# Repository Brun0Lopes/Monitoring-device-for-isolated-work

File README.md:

# Monitoring-device-for-isolated-work

This project is sponsored by JLCPCB, and will be used by workers when
they are carrying out activities in hazardous environments, to prevent
any serious accident from occurring.

Please visit https://jlcpcb.com/RAT

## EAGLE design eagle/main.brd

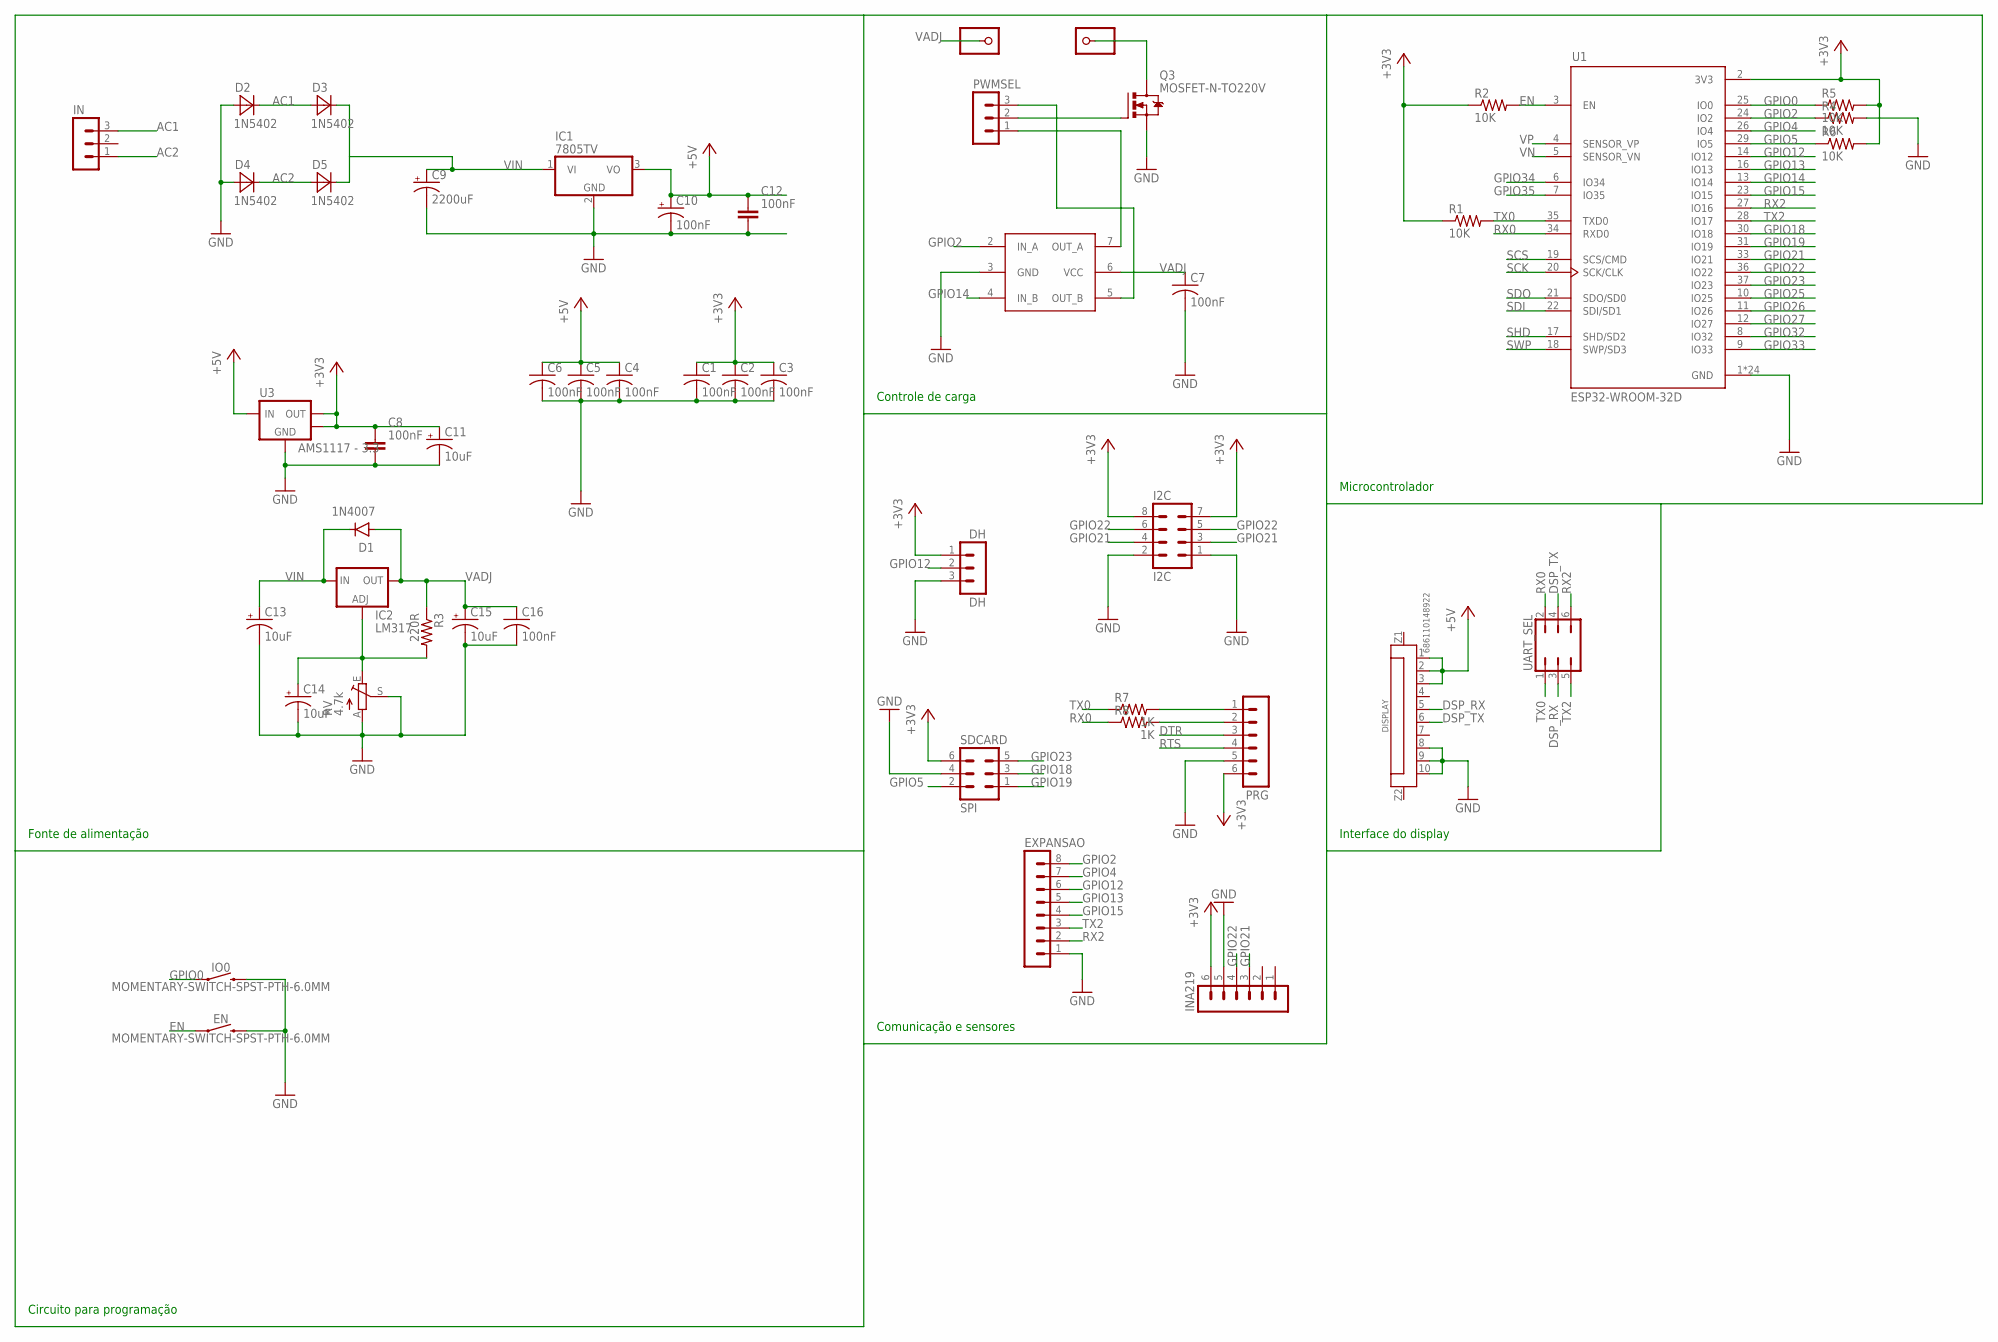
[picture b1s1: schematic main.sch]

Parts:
C1, C2, C3, C4, C5, C6, C7, C16: 100nF; C0805K
C8, C12: 100nF; CAPC2012X110
C9: 2200uF; E5-6
C10: 100nF; E2,5-5
C11, C15: 10uF; E2,5-5
C13, C14: 10uF; E2-4
D1: 1N4007; DO-41
D2, D3, D4, D5: 1N5402; DO201
DH: DH; MA03-1
DISPLAY: 686110148922
EN: MOMENTARY-SWITCH-SPST-PTH-6.0MM; TACTILE_SWITCH_PTH_6.0MM
EXPANSAO: MA08-1
I2C: I2C; MA04-2
IC1: 7805TV; TO220V
IC2: LM317; 317TS
IN: MA03-1
INA219: MA06-1
IO0: MOMENTARY-SWITCH-SPST-PTH-6.0MM; TACTILE_SWITCH_PTH_6.0MM
JP1: PINHD-1X01_2.54-S; 1X01-S
LOAD: PINHD-1X01_2.54-S; 1X01-S
PRG: MA06-1
PWMSEL: MA03-1
Q3: MOSFET-N-TO220V; TO220BV
R1, R2, R4, R5, R6: 10K; M0805
R3: 220R; 0207/5V
R7, R8: 1K; M0805
RV: 4.7k; RJ9W
SDCARD: SPI; MA03-2
U1: ESP32-WROOM-32D; MODULE_ESP32-WROOM-32D
U2: MC34151; DIL8
U3: AMS1117 - 3.3; SOT-223-3
UART_SEL: JP3Q

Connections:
+3V3: C1.1, C2.1, C3.1, C8.1, C11.+, DH.1, I2C.7, I2C.8, INA219.6, PRG.6, R1.1, R2.1, R5.2, R6.2, SDCARD.6, U1.2 (3V3), U3.2 (VOUT), U3.4 (HEATSINK)
+5V: C4.1, C5.1, C6.1, C10.+, C12.1, DISPLAY.1, DISPLAY.2, DISPLAY.3, IC1.3 (VO), U3.3 (VIN)
AC1: D2.C, D3.A, IN.3
AC2: D4.C, D5.A, IN.1
DSP_RX: DISPLAY.5, UART_SEL.3
DSP_TX: DISPLAY.6, UART_SEL.4
DTR: PRG.3
EN: EN.1, R2.2, U1.3 (EN)
GND: C1.2, C2.2, C3.2, C4.2, C5.2, C6.2, C7.2, C8.2, C9.-, C10.-, C11.-, C12.2, C13.-, C14.-, C15.-, C16.2, D2.A, D4.A, DH.3, DISPLAY.8, DISPLAY.9, DISPLAY.10, EN.3 (2), EXPANSAO.1, I2C.1, I2C.2, IC1.2 (GND), INA219.5, IO0.3 (2), PRG.5, Q3.S, R4.2, RV.A, RV.S, SDCARD.4, U1.1 (GND), U1.15 (GND), U1.38 (GND), U1.39_1 (GND), U1.39_2 (GND), U1.39_3 (GND), U1.39_4 (GND), U1.39_5 (GND), U1.39_6 (GND), U1.39_7 (GND), U1.39_8 (GND), U1.39_9 (GND), U1.39_10 (GND), U1.39_11 (GND), U1.39_12 (GND), U1.39_13 (GND), U1.39_14 (GND), U1.39_15 (GND), U1.39_16 (GND), U1.39_17 (GND), U1.39_18 (GND), U1.39_19 (GND), U1.39_20 (GND), U1.39_21 (GND), U2.3 (GND), U3.1 (GND)
GPIO0: IO0.1, R5.1, U1.25 (IO0)
GPIO2: EXPANSAO.8, R4.1, U1.24 (IO2), U2.2 (IN_A)
GPIO4: EXPANSAO.7, U1.26 (IO4)
GPIO5: R6.1, SDCARD.2, U1.29 (IO5)
GPIO12: DH.2, EXPANSAO.6, U1.14 (IO12)
GPIO13: EXPANSAO.5, U1.16 (IO13)
GPIO14: U1.13 (IO14), U2.4 (IN_B)
GPIO15: EXPANSAO.4, U1.23 (IO15)
GPIO18: SDCARD.3, U1.30 (IO18)
GPIO19: SDCARD.1, U1.31 (IO19)
GPIO21: I2C.3, I2C.4, INA219.3, U1.33 (IO21)
GPIO22: I2C.5, I2C.6, INA219.4, U1.36 (IO22)
GPIO23: SDCARD.5, U1.37 (IO23)
GPIO25: U1.10 (IO25)
GPIO26: U1.11 (IO26)
GPIO27: U1.12 (IO27)
GPIO32: U1.8 (IO32)
GPIO33: U1.9 (IO33)
GPIO34: U1.6 (IO34)
GPIO35: U1.7 (IO35)
unnamed: PRG.1, R7.2
unnamed: PRG.2, R8.2
unnamed: C14.+, IC2.1 (ADJ), R3.2, RV.E
unnamed: PWMSEL.1, U2.7 (OUT_A)
unnamed: PWMSEL.3, U2.5 (OUT_B)
unnamed: LOAD.1, Q3.D
unnamed: PWMSEL.2, Q3.G
RTS: PRG.4
RX0: R8.1, U1.34 (RXD0), UART_SEL.2
RX2: EXPANSAO.2, U1.27 (IO16), UART_SEL.6
SCK: U1.20 (SCK/CLK)
SCS: U1.19 (SCS/CMD)
SDI: U1.22 (SDI/SD1)
SDO: U1.21 (SDO/SD0)
SHD: U1.17 (SHD/SD2)
SWP: U1.18 (SWP/SD3)
TX0: R1.2, R7.1, U1.35 (TXD0), UART_SEL.1
TX2: EXPANSAO.3, U1.28 (IO17), UART_SEL.5
VADJ: C7.1, C15.+, C16.1, D1.A, IC2.2 (OUT), JP1.1, R3.1, U2.6 (VCC)
VIN: C9.+, C13.+, D1.C, D3.C, D5.C, IC1.1 (VI), IC2.3 (IN)
VN: U1.5 (SENSOR_VN)
VP: U1.4 (SENSOR_VP)

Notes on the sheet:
Fonte de alimentação
Circuito para programação
Controle de carga
Comunicação e sensores
Microcontrolador
Interface do display

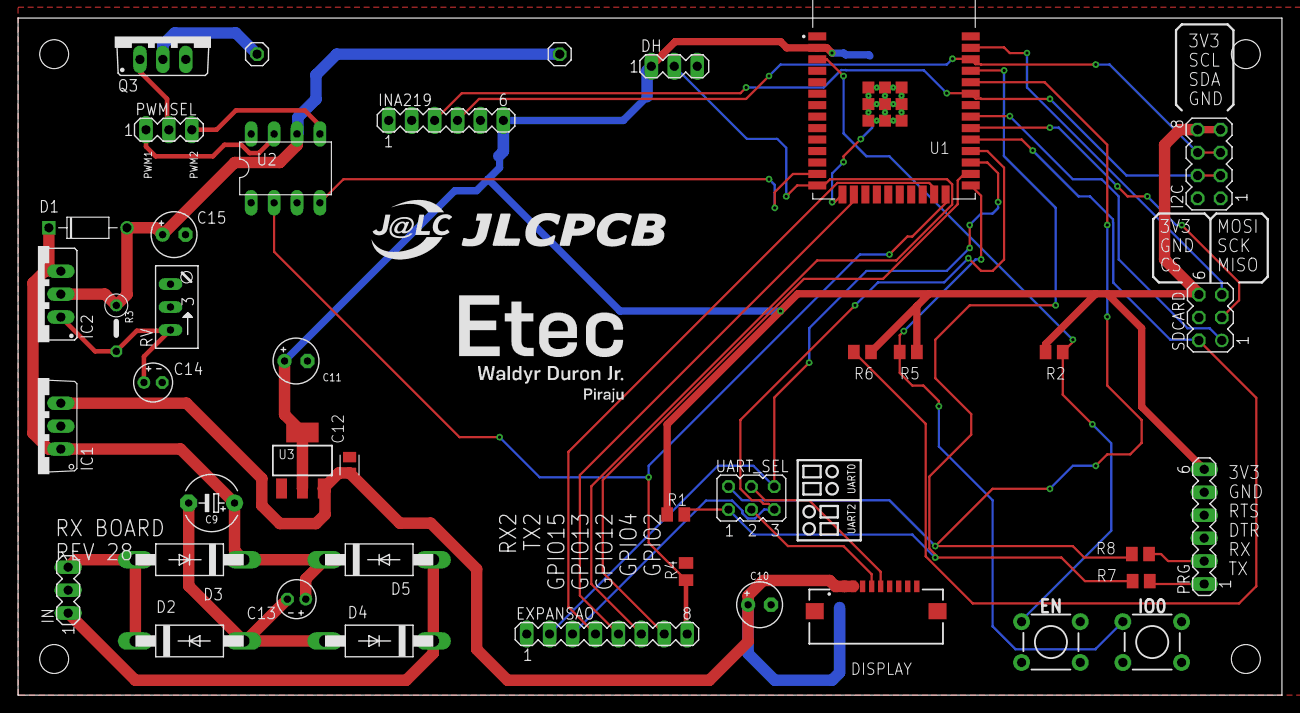
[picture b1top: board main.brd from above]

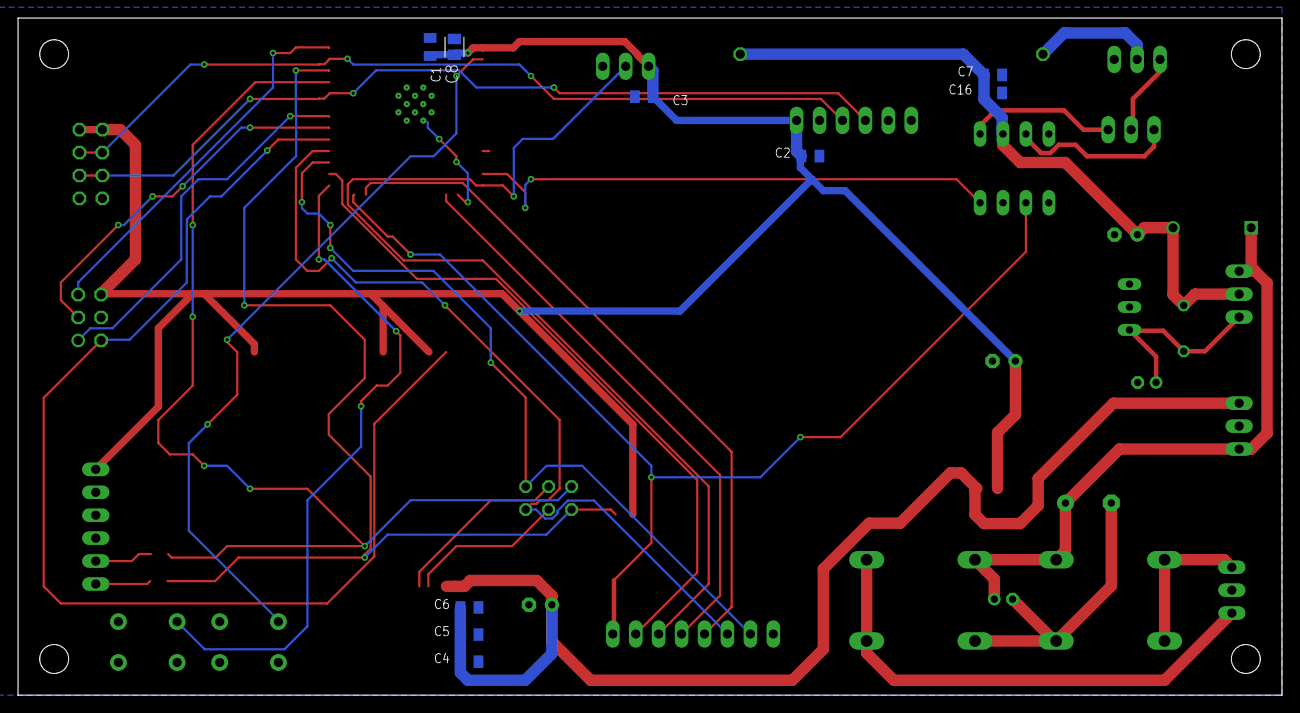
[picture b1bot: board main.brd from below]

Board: 2 copper layers, 140.0 x 75.0 mm, 50 parts (9 on the bottom side), 34 nets.

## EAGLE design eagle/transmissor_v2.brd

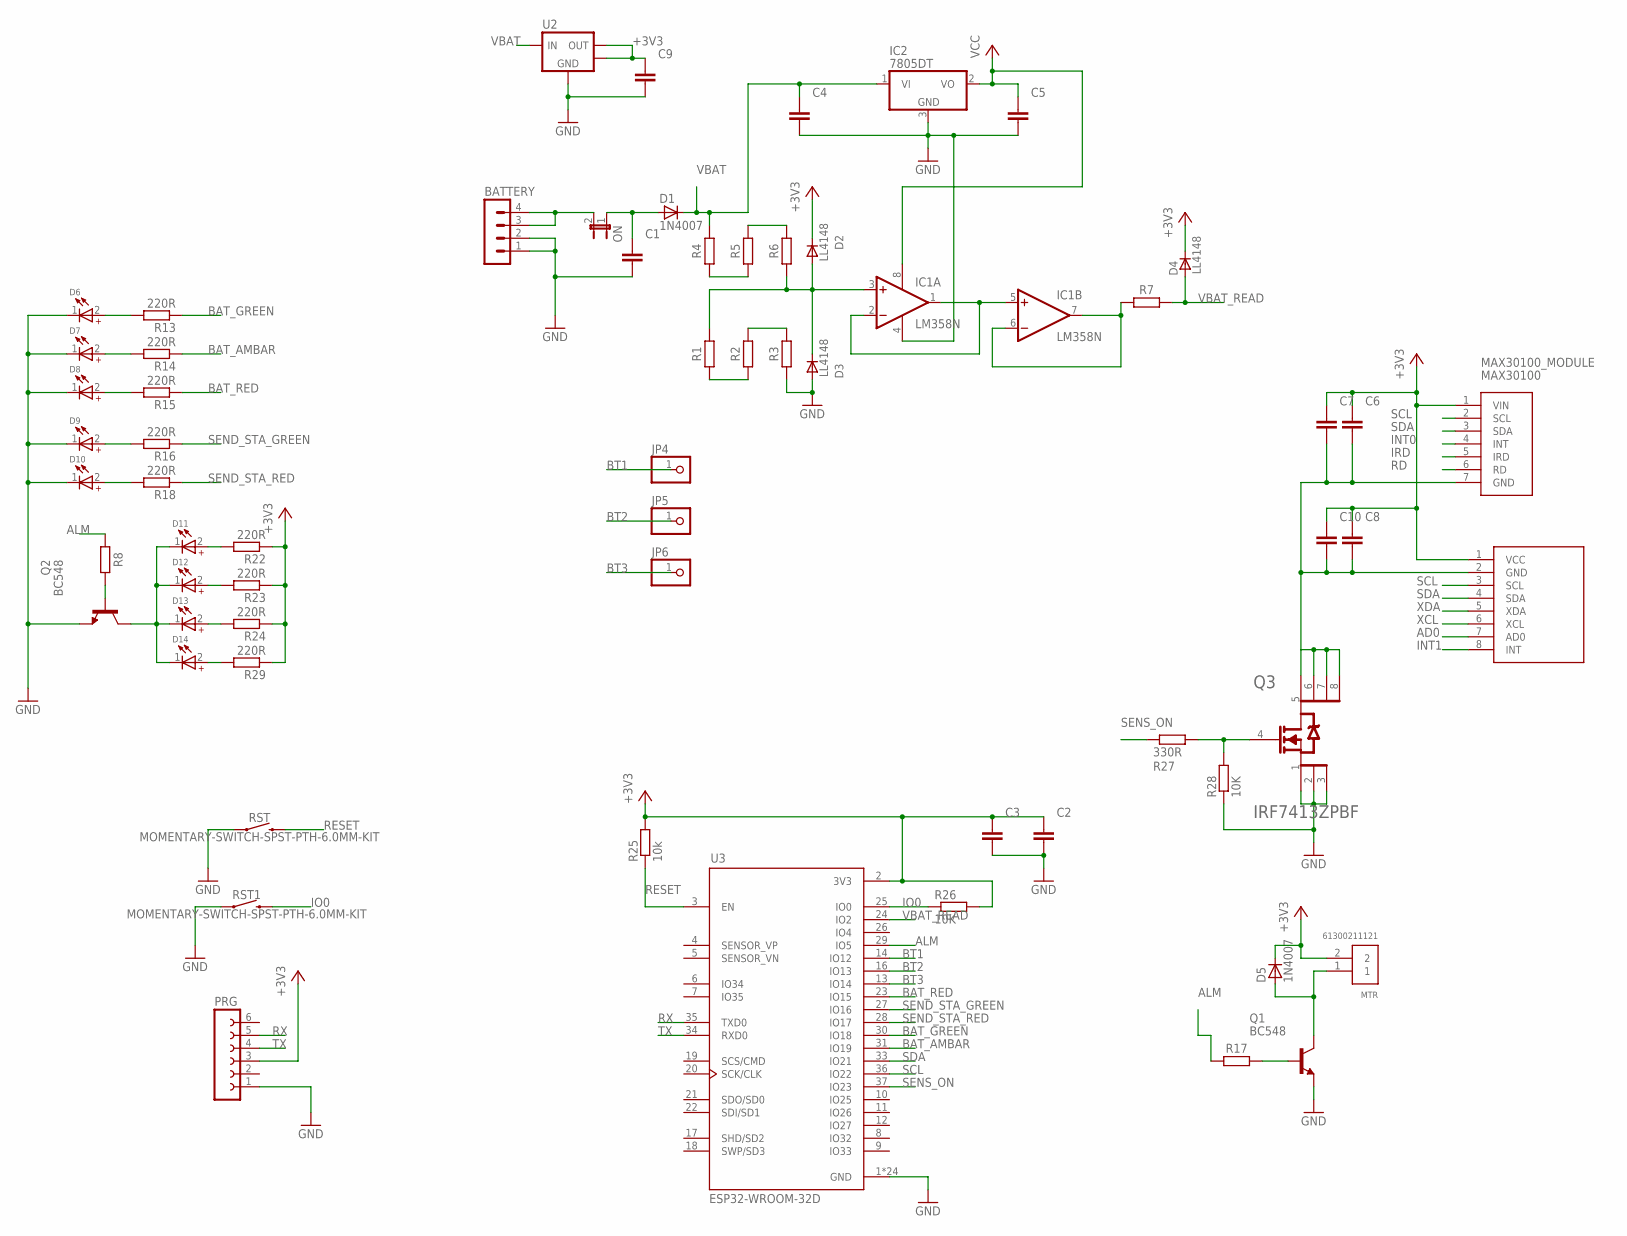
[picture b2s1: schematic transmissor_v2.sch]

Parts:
BATTERY: MA04-1
C1, C2, C3, C4, C5, C6, C7, C8, C9, C10: 100nF; CAPC2012X110
D1, D5: 1N4007; SMA
D2, D3, D4: LL4148; SOD80_DO213AA_MINIMELF
D6, D9: WL-SMCW_0805_150080GS75000; WL-SMCW_0805
D7: WL-SMCW_0805_150080AS75000; WL-SMCW_0805
D8, D10, D11, D12, D13, D14: WL-SMCW_0805_150080RS75000; WL-SMCW_0805
IC1: LM358N; DIL08
IC2: 7805DT; TO252
JP4, JP5, JP6: PINHD-1X1; 1X01
MAX30100: MAX30100_MODULE; MODULE1
MPU6050: MPU6050MODULE; MODULE2
MTR: 61300211121
ON: JP1E; JP1
PRG: FE06-1; FE06
Q1, Q2: BC548; TO92-EBC
Q3: INFINEON_IRF7413ZPBFINFINEON_IRF7413ZPBF_0_0; INFINEON_IRF7413ZPBF_0
R1, R2: 2K; RESC2012X65
R3, R7: 100R; RESC2012X65
R4, R5: 3.3K; RESC2012X65
R6: 470R; RESC2012X65
R8, R17: 330R; RESC2012X65
R13, R14, R15, R16, R18, R22, R23, R24, R29: 220R; R0805
R25: 10k; R0805
R26, R28: 10K; R0805
R27: 330R; R0805
RST, RST1: MOMENTARY-SWITCH-SPST-PTH-6.0MM-KIT; TACTILE_SWITCH_PTH_6.0MM_KIT
U2: LM1117-SOT223; SOT-223-3
U3: ESP32-WROOM-32D; MODULE_ESP32-WROOM-32D

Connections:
+3V3: C2.1, C3.1, C6.1, C7.1, C8.1, C9.1, C10.1, D2.C, D4.C, D5.K (C), MAX30100.1 (VIN), MPU6050.1 (VCC), MTR.2, PRG.3, R22.1, R23.1, R24.1, R25.2, R26.2, R29.1, U2.2 (VOUT), U2.4 (HEATSINK), U3.2 (3V3)
AD0: MPU6050.7 (AD0)
ALM: R8.1, R17.1, U3.29 (IO5)
BAT_AMBAR: R14.1, U3.31 (IO19)
BAT_GREEN: R13.1, U3.30 (IO18)
BAT_RED: R15.1, U3.23 (IO15)
BT1: JP4.1, U3.14 (IO12)
BT2: JP5.1, U3.16 (IO13)
BT3: JP6.1, U3.13 (IO14)
GND: BATTERY.1, BATTERY.2, C1.2, C2.2, C3.2, C4.2, C5.2, C9.2, D3.A, D6.1 (-), D7.1 (-), D8.1 (-), D9.1 (-), D10.1 (-), IC1.4 (V-), IC2.3 (GND), PRG.1, Q1.E, Q2.E, Q3.1 (1_S), Q3.2 (2_S), Q3.3 (3_S), R3.1, R28.1, RST.1, RST1.1, U2.1 (GND), U3.1 (GND), U3.15 (GND), U3.38 (GND), U3.39_1 (GND), U3.39_2 (GND), U3.39_3 (GND), U3.39_4 (GND), U3.39_5 (GND), U3.39_6 (GND), U3.39_7 (GND), U3.39_8 (GND), U3.39_9 (GND), U3.39_10 (GND), U3.39_11 (GND), U3.39_12 (GND), U3.39_13 (GND), U3.39_14 (GND), U3.39_15 (GND), U3.39_16 (GND), U3.39_17 (GND), U3.39_18 (GND), U3.39_19 (GND), U3.39_20 (GND), U3.39_21 (GND)
INT0: MAX30100.4 (INT)
INT1: MPU6050.8 (INT)
IO0: R26.1, RST1.3 (2), U3.25 (IO0)
IRD: MAX30100.5 (IRD)
unnamed: BATTERY.3, BATTERY.4, ON.2
unnamed: C1.1, D1.A, ON.1
unnamed: IC1.6 (-IN), IC1.7 (OUT), R7.1
unnamed: R4.1, R5.1
unnamed: R5.2, R6.2
unnamed: D2.A, D3.C, IC1.3 (+IN), R1.2, R6.1
unnamed: R1.1, R2.1
unnamed: R2.2, R3.2
unnamed: Q3.4 (G), R27.2, R28.2
unnamed: C6.2, C7.2, C8.2, C10.2, MAX30100.7 (GND), MPU6050.2 (GND), Q3.5 (1_D), Q3.6 (2_D), Q3.7 (3_D), Q3.8 (4_D)
unnamed: D6.2 (+), R13.2
unnamed: D7.2 (+), R14.2
unnamed: D8.2 (+), R15.2
unnamed: D5.A, MTR.1, Q1.C
unnamed: Q1.B, R17.2
unnamed: IC1.1 (OUT), IC1.2 (-IN), IC1.5 (+IN)
unnamed: Q2.B, R8.2
unnamed: D9.2 (+), R16.2
unnamed: D10.2 (+), R18.2
unnamed: D11.1 (-), D12.1 (-), D13.1 (-), D14.1 (-), Q2.C
unnamed: D11.2 (+), R22.2
unnamed: D12.2 (+), R23.2
unnamed: D13.2 (+), R24.2
unnamed: D14.2 (+), R29.2
RD: MAX30100.6 (RD)
RESET: R25.1, RST.3 (2), U3.3 (EN)
RX: PRG.5, U3.35 (TXD0)
SCL: MAX30100.2 (SCL), MPU6050.3 (SCL), U3.36 (IO22)
SDA: MAX30100.3 (SDA), MPU6050.4 (SDA), U3.33 (IO21)
SEND_STA_GREEN: R16.1, U3.27 (IO16)
SEND_STA_RED: R18.1, U3.28 (IO17)
SENS_ON: R27.1, U3.37 (IO23)
TX: PRG.4, U3.34 (RXD0)
VBAT: C4.1, D1.K (C), IC2.1 (VI), R4.2, U2.3 (VIN)
VBAT_READ: D4.A, R7.2, U3.24 (IO2)
VCC: C5.1, IC1.8 (V+), IC2.2 (VO)
XCL: MPU6050.6 (XCL)
XDA: MPU6050.5 (XDA)

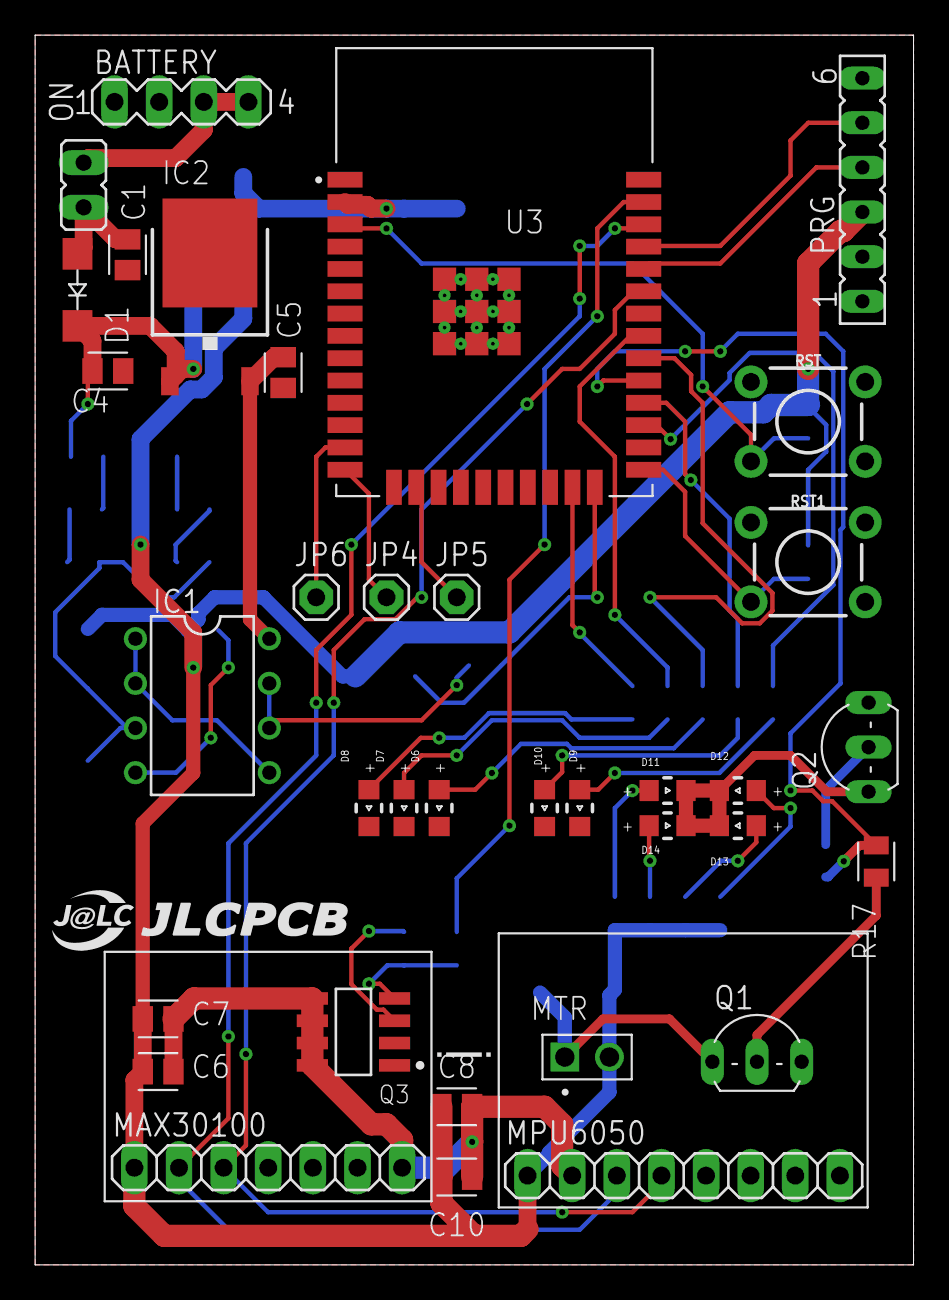
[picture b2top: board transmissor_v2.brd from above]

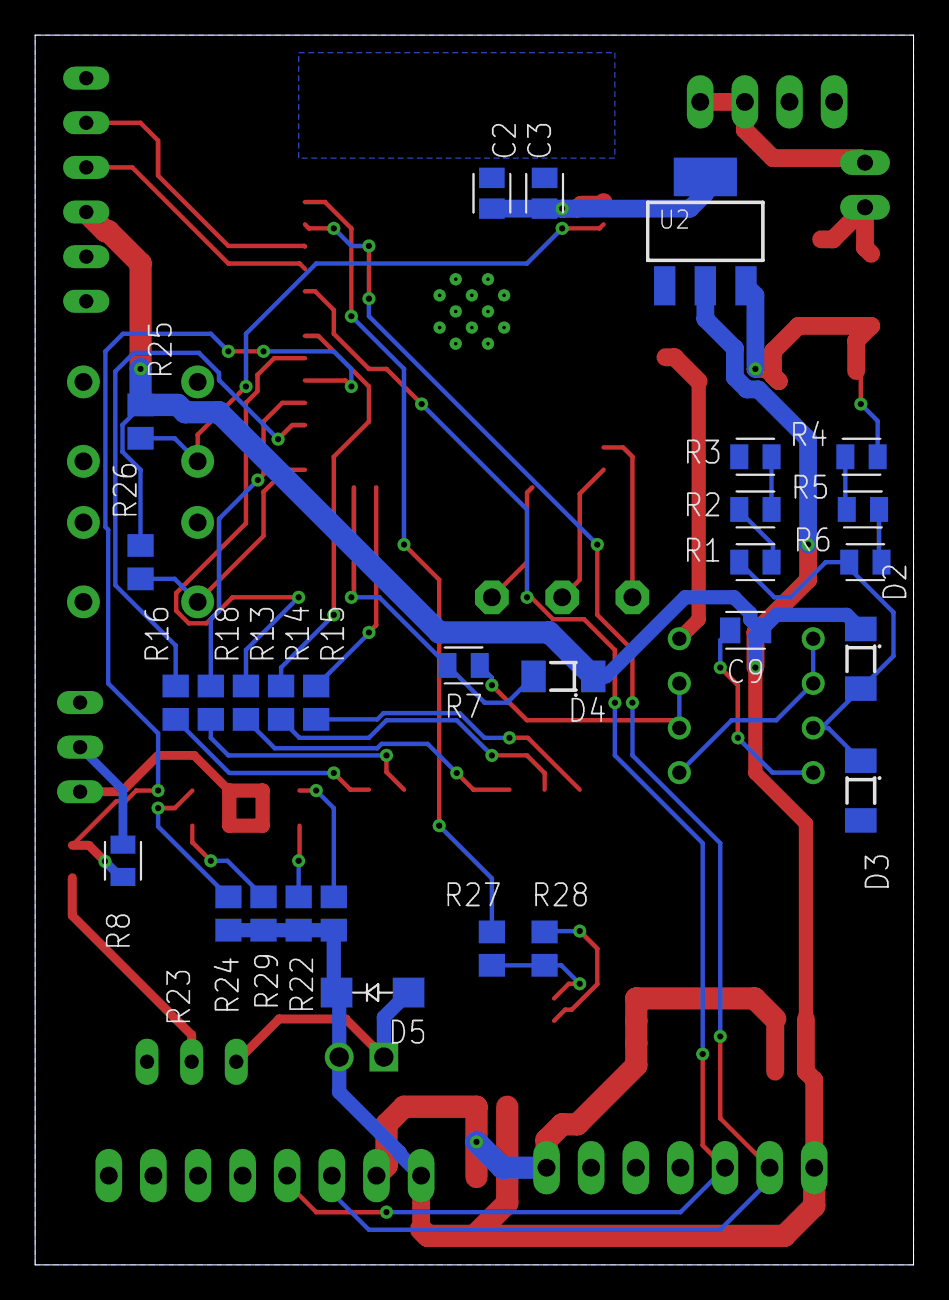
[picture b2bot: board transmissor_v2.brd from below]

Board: 2 copper layers, 50.0 x 70.0 mm, 64 parts (29 on the bottom side), 45 nets.

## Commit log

2021-05-27 Organizing files
2021-06-26 Prototype version
2021-11-02 gerber files uploaded

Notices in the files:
parts and their libraries:
Wurth_Connectors_WR-FPC: Copyright: Würth Elektronik
SparkFun-Switches: Licensing: Creative Commons ShareAlike 4.0 International - https://creativecommons.org/licenses/by-sa/4.0
